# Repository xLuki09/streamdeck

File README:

A custom Macro Pad with 9 switches and a rotary encoder with buttonfunktion all controlled by an esp32 USB-C. Built on a custom PCB 
SOnn there will be a 3D modell for the casing and the source code

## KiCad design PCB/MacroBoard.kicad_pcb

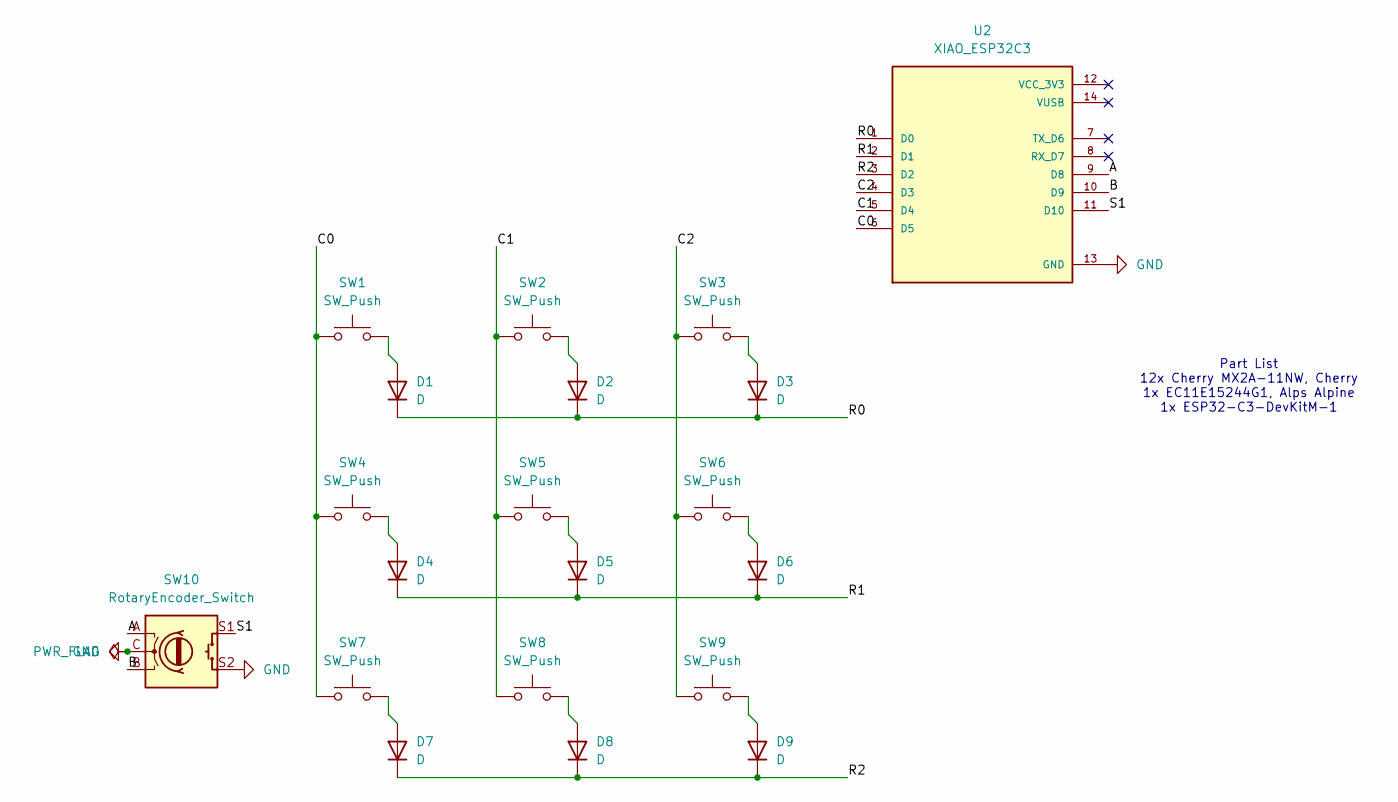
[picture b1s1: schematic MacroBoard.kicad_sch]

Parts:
D1, D2, D3, D4, D5, D6, D7, D8, D9: D; D_DO-35_SOD27_P7.62mm_Horizontal
SW1, SW2, SW3, SW4, SW5, SW6, SW7, SW8, SW9: SW_Push; SW_Cherry_MX_1.00u_PCB
SW10: RotaryEncoder_Switch; RotaryEncoder_Alps_EC11E-Switch_Vertical_H20mm
U2: XIAO_ESP32C3; MODULE_XIAO_ESP32C3; PARTREV 23/05/2022

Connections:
/A: SW10.A, U2.9 (D8)
/B: SW10.B, U2.10 (D9)
/C0: SW1.1, SW4.1, SW7.1, U2.6 (D5)
/C1: SW2.1, SW5.1, SW8.1, U2.5 (D4)
/C2: SW3.1, SW6.1, SW9.1, U2.4 (D3)
/R0: D1.1 (K), D2.1 (K), D3.1 (K), U2.1 (D0)
/R1: D4.1 (K), D5.1 (K), D6.1 (K), U2.2 (D1)
/R2: D7.1 (K), D8.1 (K), D9.1 (K), U2.3 (D2)
/S1: SW10.S1, U2.11 (D10)
GND: SW10.C, SW10.S2, U2.13 (GND)
unnamed: D1.2 (A), SW1.2
unnamed: D2.2 (A), SW2.2
unnamed: D3.2 (A), SW3.2
unnamed: D4.2 (A), SW4.2
unnamed: D5.2 (A), SW5.2
unnamed: D6.2 (A), SW6.2
unnamed: D7.2 (A), SW7.2
unnamed: D8.2 (A), SW8.2
unnamed: D9.2 (A), SW9.2

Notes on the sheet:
Part List 12x Cherry MX2A-11NW, Cherry 1x EC11E15244G1, Alps Alpine 1x ESP32-C3-DevKitM-1

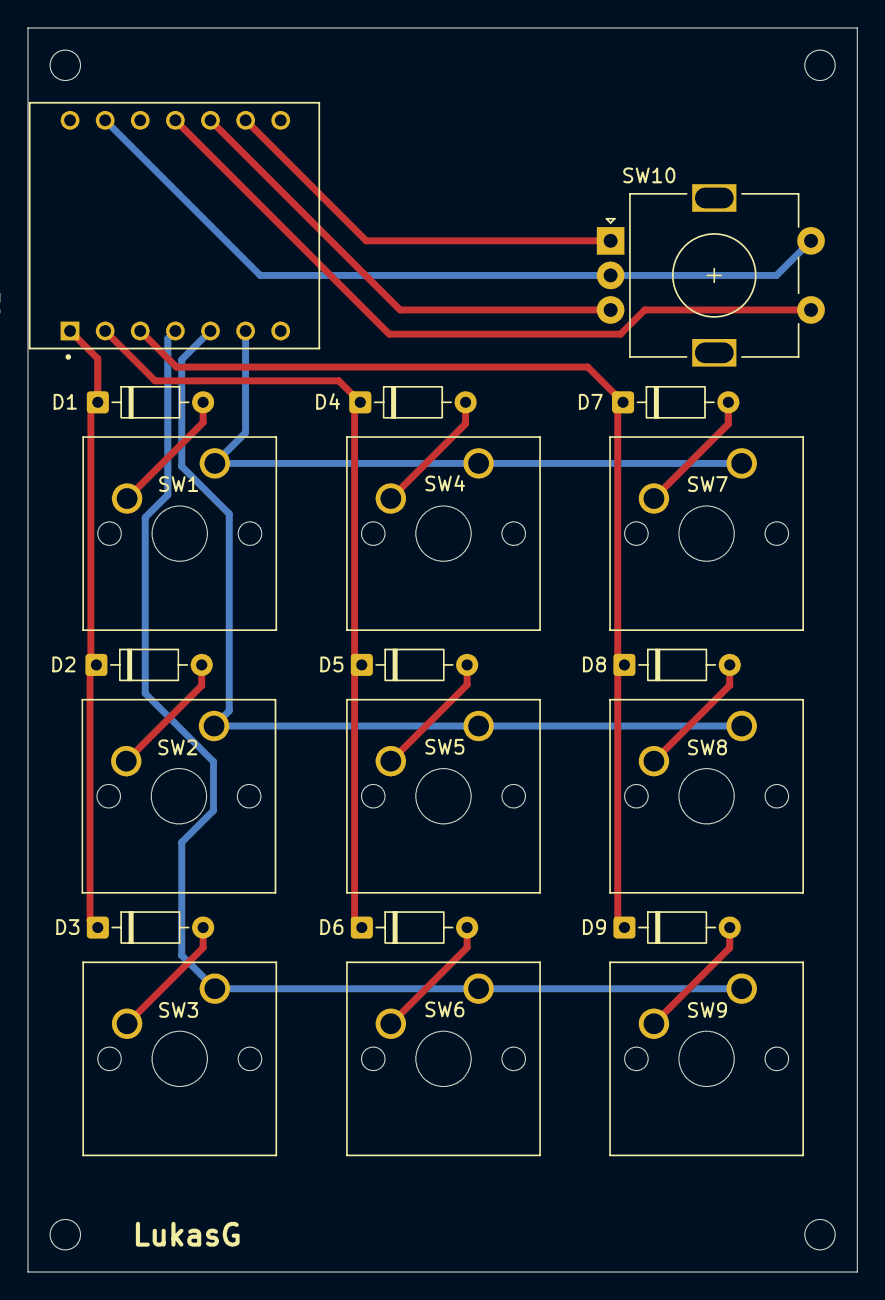
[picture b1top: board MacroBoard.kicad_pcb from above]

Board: 2 copper layers, 60.0 x 90.0 mm, 20 parts (0 on the bottom side), 19 nets.

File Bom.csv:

ID;Bezeichner;Footprint;Stückzahl;Bezeichnung;Anbieter und Referenz;
1;D1, D2, D3, D4, D5, D6, D7, D8, D9;D_DO-35_SOD27_P7.62mm_Horizontal;9;D;https://de.farnell.com/multicomp-pro/1n4148-do-35/kleinsigna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;
2;SW1, SW2, SW3, SW4, SW5, SW6, SW7, SW8, SW9;SW_Cherry_MX_1.00u_PCB;9;SW_Push;https://www.reichelt.com/de/en/shop/product/cherry_mx_red_ke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;
3;SW10;RotaryEncoder_Alps_EC11E-Switch_Vertical_H20mm;1;RotaryEncoder_Switch;https://www.mouser.at/de/ProductDetail/Same-Sky/RIC11-31S20D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;
4;U2;MODULE_XIAO_ESP32C3;1;XIAO_ESP32C3;https://www.tme.eu/en/details/seeed-113991054/development-ki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;
